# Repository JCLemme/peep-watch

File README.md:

# peep watch

I'm attempting to build some real nice rebbleos hardware. 

---

## the watches

Right now there's just the "big board" prototype. After that there'll be a smaller prototype that can actually be worn on the body and then, hopefully, an actually small watch. (assuming all the prototypes work as designed lol).

## contributing

Hit me up on the discord, documentation is still pretty light.

Datasheets go in ./common/datasheets, kicad libraries in ./common/kicad-libs. I've been using the nightly kicad 5.99 builds.

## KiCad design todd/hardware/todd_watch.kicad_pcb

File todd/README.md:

# "todd" prototype watch

Ok so this is the "big board" prototype. Everything broken out, huge pcb, erring on the side of excess, etc. Hopefully this design can just be taken and crammed onto a tiny lil board when we're ready to make some wearable prototypes.

[See the schematic here](./sch_export/todd_watch.pdf)

---

## theory of design

I'm trying to not stray too far from the designs of the original run of pebbles. I'm all in for messing with the "formula" in the future but right now we need more of the same, yeah? With that in mind the feature set hits the same notes:

* 32bit ARM cpu @ 128mhz with ~512k RAM
* 64mb flash storage
* JDI memory-in-pixel transflective LCD
* Four buttons
* IMU with magnetometer, gyroscope, etc.
* Microphone

It's a good starting place anyway. I'm not too worried about part commonality (practical reasons, the pebbles are getting up there in years) and once I abandoned that mindset things got wild. With that in mind -

## the changes

In no particular order

* The cpu was switched over from an STM32 to a shiny new Nordic part, the nRF5340. Along with the obvious improvements - more memory, more flash, more faster - it's a combo cpu + bluetooth part, so we don't need a separate bluetooth chip. It also has a dedicated networking core which might be useful for power reduction going forward.
* The display is a 176x176 model, up from 168x144. It's the closest display I could find to the originals.
* The IMU has a magnetometer built in - one fewer chip.
* The PMIC includes all the battery hardware, plus a haptic controller. Also about that -
* Swapped the ERM vibration motor for a linear resonant actuator. Welcome to the future bay bee
* NFC is also built into the cpu, so tap to pay might be a potential feature. Maybe. Hopefully.

## back to theory

I'd like this design to stay relevant and sourceable for a while so I'm choosing parts by what I can trust will be available long term. As of right now all the parts chosen are in stock at digikey, normally stocked by digikey, and have at least five years of availability on the roadmap. (Save for the display - it's in stock at arrow right now but it's a weird part with no good replacement so).

The board is gonna be big to support all the extra jumpers and breakouts and whatnot but it's gonna use the same packages (ideally) as the small version. These are gonna be nasty little BGAs and QFNs which means that most people won't be able to build one but them's the breaks. When everything is working I'm down to do a little manufacturing run with my oven, get some hardware to people.

---

## so does it work

Not yet

## when will it work

June, probably

## what's done

Schematic is looking good. Working on BOM and footprints now

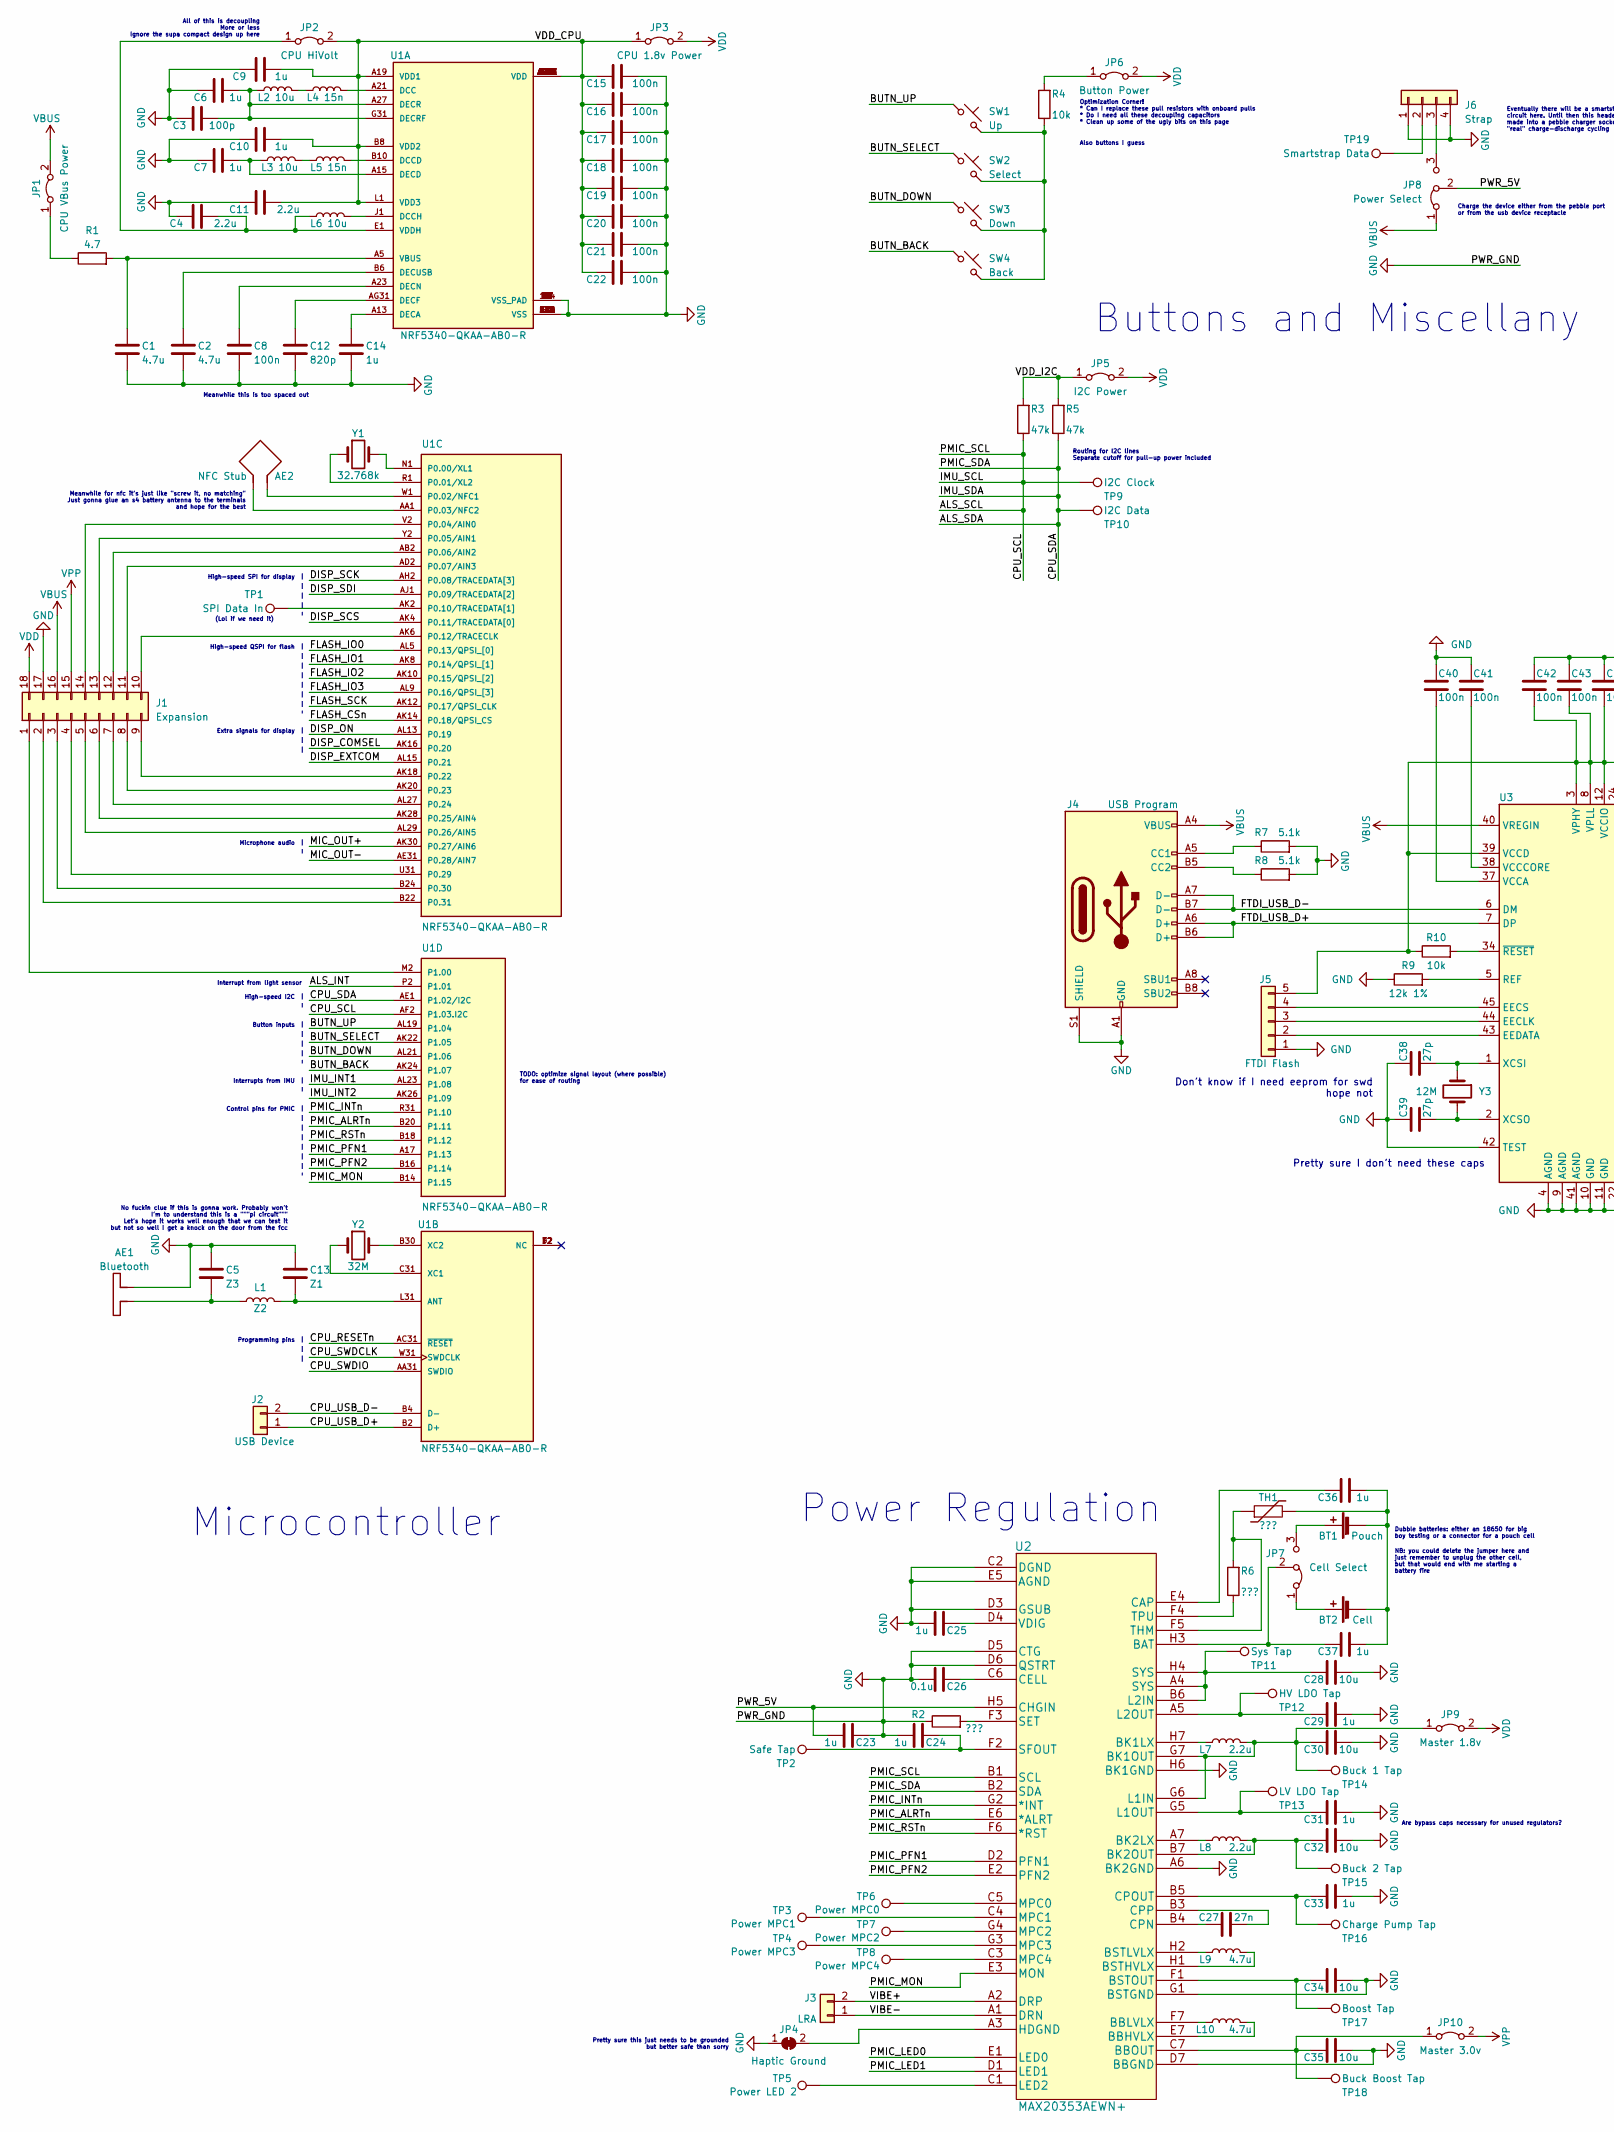
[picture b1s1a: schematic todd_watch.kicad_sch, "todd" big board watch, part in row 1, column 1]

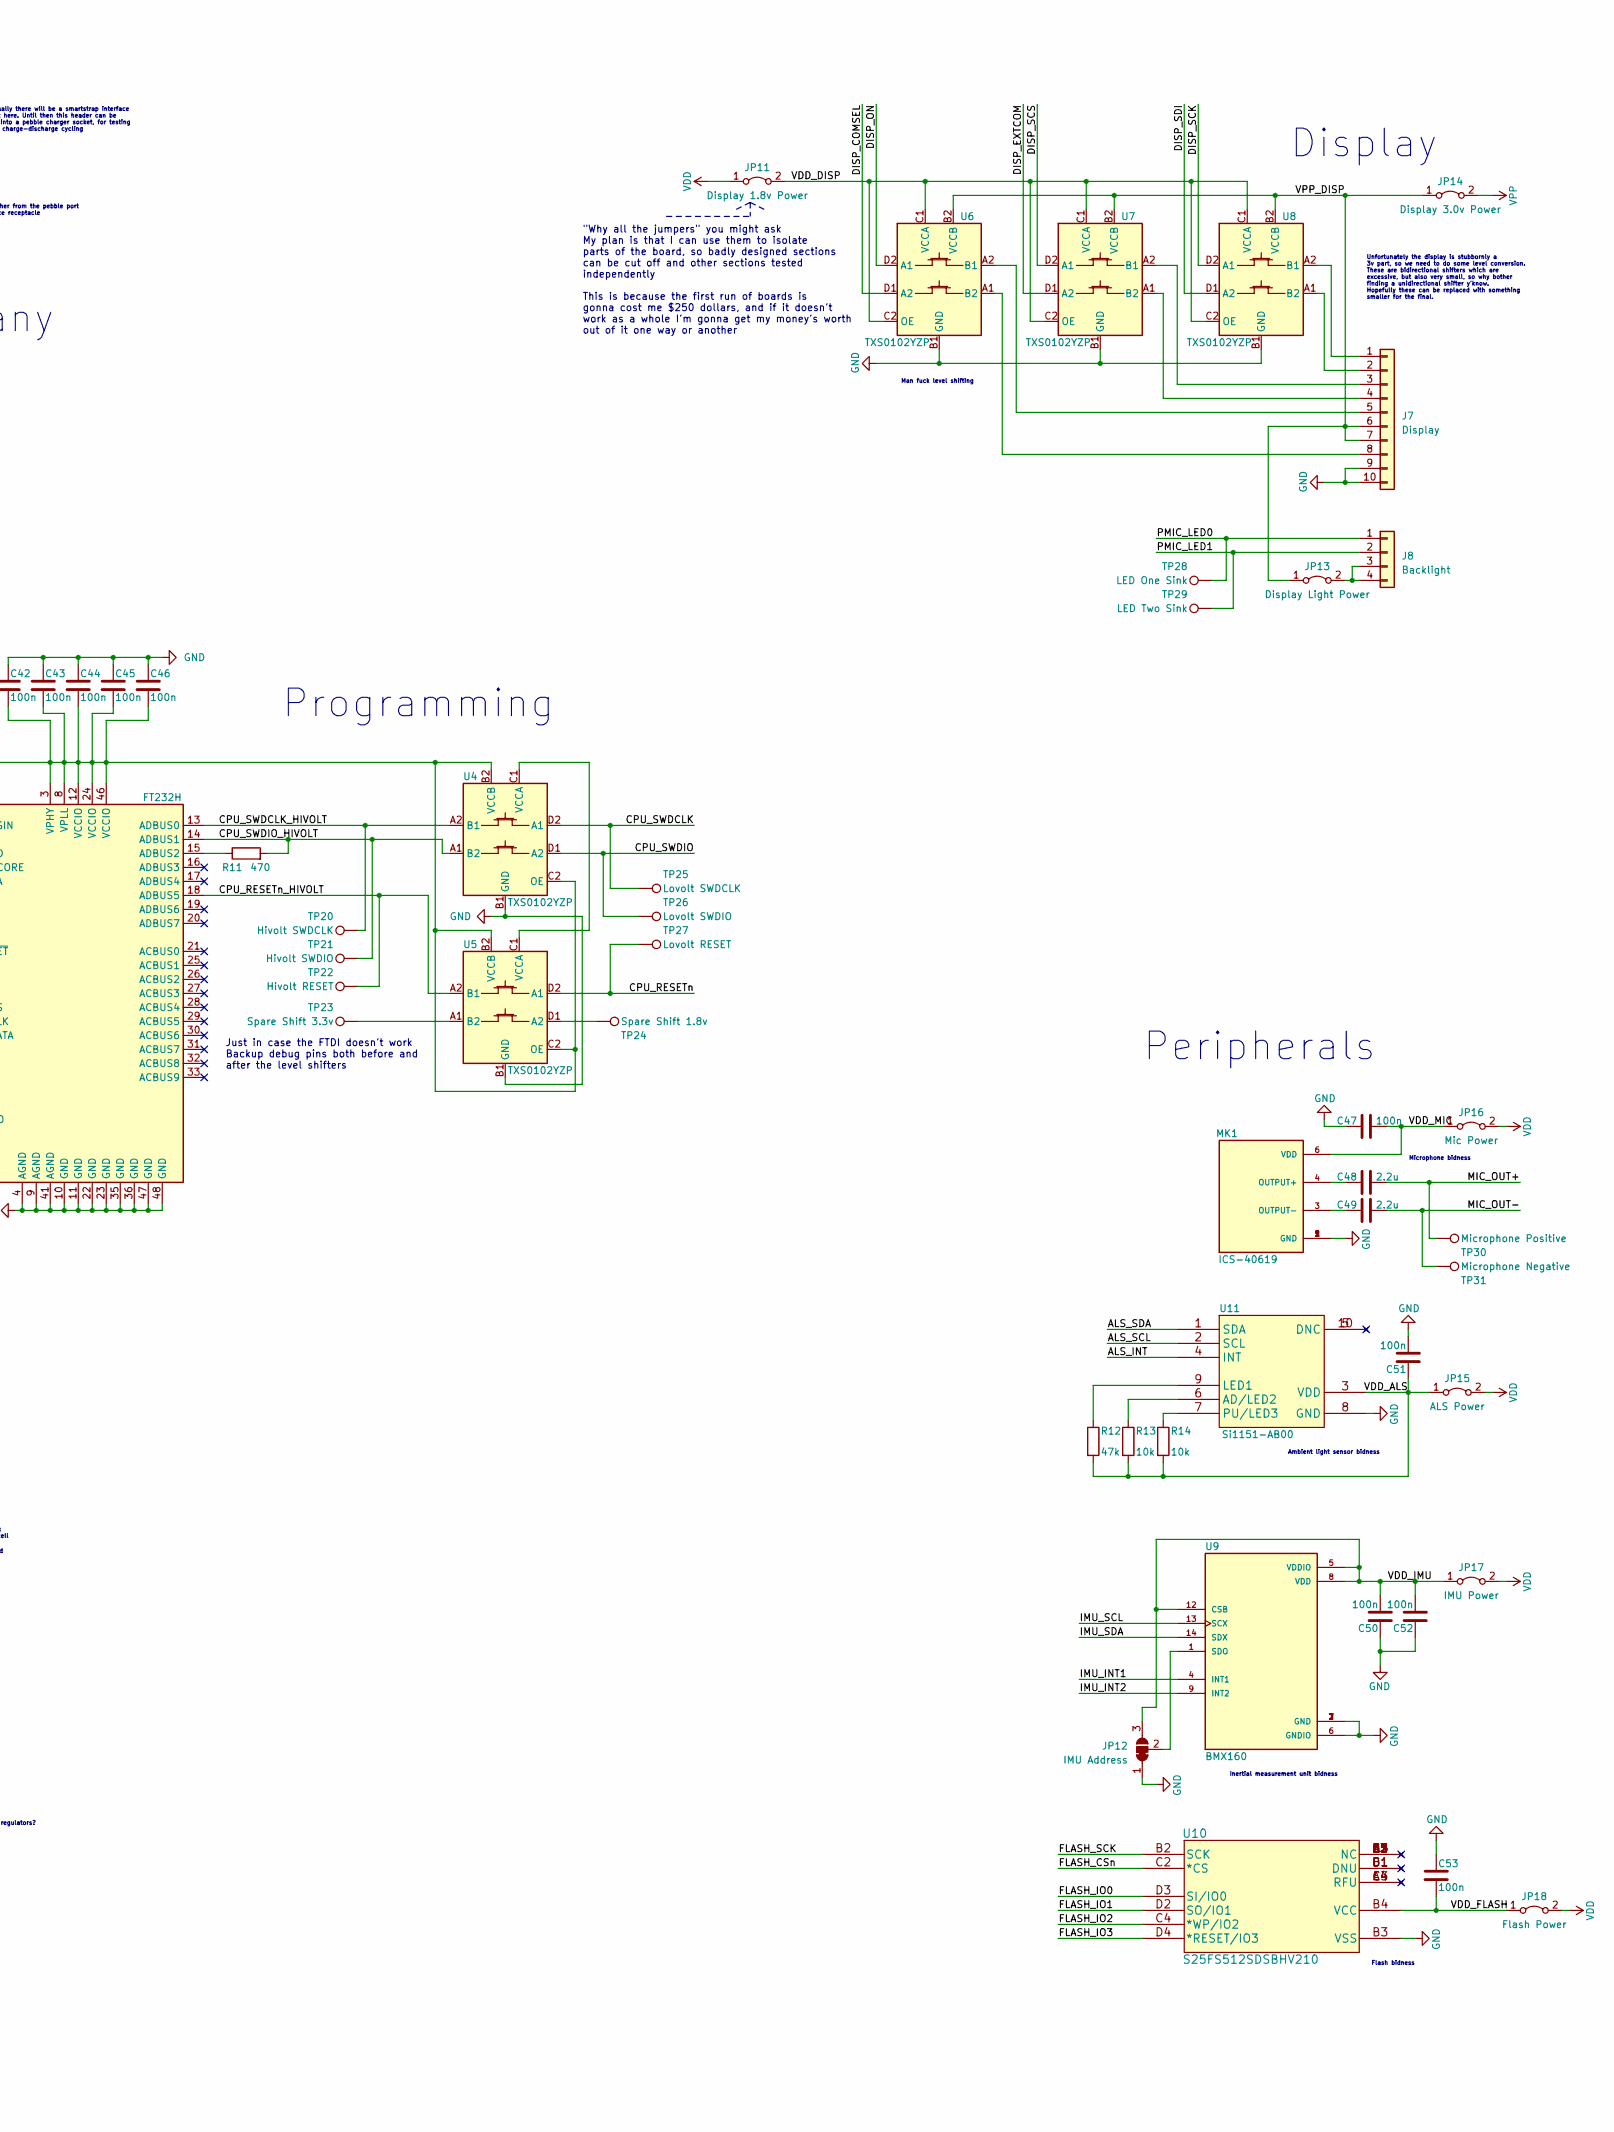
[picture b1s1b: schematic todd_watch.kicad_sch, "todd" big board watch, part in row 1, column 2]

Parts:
AE1: Bluetooth; Texas_SWRA117D_2.4GHz_Left
AE2: NFC Stub; R_1206_3216Metric_Pad1.30x1.75mm_HandSolder
BT1: Pouch; PinSocket_1x02_P2.54mm_Vertical
BT2: Cell; BatteryHolder_Keystone_1042_1x18650
C1, C2: 4.7u; C_0603_1608Metric
C3: 100p; C_0603_1608Metric
C4, C11, C48, C49: 2.2u; C_0603_1608Metric
C5: Z3; C_0603_1608Metric
C6, C7, C9, C10, C14, C23, C24, C25, C29, C31, C33, C36, C37: 1u; C_0603_1608Metric
C8, C15, C16, C17, C18, C19, C20, C21, C22, C40, C41, C42, C43, C44, C45, C46, C47, C50, C51, C52, C53: 100n; C_0603_1608Metric
C12: 820p; C_0603_1608Metric
C13: Z1; C_0603_1608Metric
C26: 0.1u; C_0603_1608Metric
C27: 27n; C_0603_1608Metric
C28, C30, C32, C34, C35: 10u; C_0603_1608Metric
C38, C39: 27p; C_0603_1608Metric
J1: Expansion; PinSocket_2x09_P1.27mm_Vertical
J2: USB Device
J3: LRA; PinHeader_1x02_P2.54mm_Vertical
J4: USB Program; USB_C_Receptacle_XKB_U262-16XN-4BVC11
J5: FTDI Flash; PinHeader_1x05_P1.27mm_Vertical
J6: Strap; PinHeader_1x04_P2.54mm_Vertical
J7: Display; Hirose_FH12-10S-0.5SH_1x10-1MP_P0.50mm_Horizontal
J8: Backlight
JP1: CPU VBus Power; PinHeader_2x01_P1.27mm_Horizontal
JP2: CPU HiVolt; PinHeader_2x01_P1.27mm_Horizontal
JP3: CPU 1.8v Power; PinHeader_2x01_P1.27mm_Horizontal
JP4: Haptic Ground; SolderJumper-2_P1.3mm_Open_TrianglePad1.0x1.5mm
JP5: I2C Power; PinHeader_2x01_P1.27mm_Horizontal
JP6: Button Power; PinHeader_2x01_P1.27mm_Horizontal
JP7: Cell Select; PinHeader_1x03_P1.27mm_Horizontal
JP8: Power Select; PinHeader_1x03_P1.27mm_Horizontal
JP9: Master 1.8v; PinHeader_2x01_P1.27mm_Horizontal
JP10: Master 3.0v; PinHeader_1x02_P1.27mm_Horizontal
JP11: Display 1.8v Power; PinHeader_1x02_P1.27mm_Horizontal
JP12: IMU Address; SolderJumper-3_P2.0mm_Open_TrianglePad1.0x1.5mm_NumberLabels
JP13: Display Light Power; PinHeader_1x02_P1.27mm_Horizontal
JP14: Display 3.0v Power; PinHeader_1x02_P1.27mm_Horizontal
JP15: ALS Power; PinHeader_1x02_P1.27mm_Horizontal
JP16: Mic Power; PinHeader_1x02_P1.27mm_Horizontal
JP17: IMU Power; PinHeader_1x02_P1.27mm_Horizontal
JP18: Flash Power; PinHeader_1x02_P1.27mm_Horizontal
L1: Z2; L_0603_1608Metric
L2, L3, L6: 10u; L_0603_1608Metric
L4, L5: 15n; L_0603_1608Metric
L7, L8: 2.2u; L_0603_1608Metric
L9, L10: 4.7u; L_0603_1608Metric
MK1: ICS-40619; MIC_ICS-40619; PARTREV 1.0
R1: 4.7; R_0603_1608Metric
R2, R6: ???; R_0603_1608Metric
R3, R5, R12: 47k; R_0603_1608Metric
R4, R10, R13, R14: 10k; R_0603_1608Metric
R7, R8: 5.1k; R_0603_1608Metric
R9: 12k 1%; R_0603_1608Metric
R11: 470; R_0603_1608Metric
SW1: Up; SW_PUSH_6mm
SW2: Select; SW_PUSH_6mm
SW3: Down; SW_PUSH_6mm
SW4: Back; SW_PUSH_6mm
TH1: ???; C_0603_1608Metric
TP1: SPI Data In; TestPoint_Pad_D1.0mm
TP2: Safe Tap; TestPoint_Pad_D1.0mm
TP3: Power MPC1; TestPoint_Pad_D1.0mm
TP4: Power MPC3; TestPoint_Pad_D1.0mm
TP5: Power LED 2; TestPoint_Pad_D1.0mm
TP6: Power MPC0; TestPoint_Pad_D1.0mm
TP7: Power MPC2; TestPoint_Pad_D1.0mm
TP8: Power MPC4; TestPoint_Pad_D1.0mm
TP9: I2C Clock; TestPoint_Pad_D1.0mm
TP10: I2C Data; TestPoint_Pad_D1.0mm
TP11: Sys Tap; TestPoint_Pad_D1.0mm
TP12: HV LDO Tap; TestPoint_Pad_D1.0mm
TP13: LV LDO Tap; TestPoint_Pad_D1.0mm
TP14: Buck 1 Tap; TestPoint_Pad_D1.0mm
TP15: Buck 2 Tap; TestPoint_Pad_D1.0mm
TP16: Charge Pump Tap; TestPoint_Pad_D1.0mm
TP17: Boost Tap; TestPoint_Pad_D1.0mm
TP18: Buck Boost Tap; TestPoint_Pad_D1.0mm
TP19: Smartstrap Data; TestPoint_Pad_D1.0mm
TP20: Hivolt SWDCLK; TestPoint_Pad_D1.0mm
TP21: Hivolt SWDIO; TestPoint_Pad_D1.0mm
TP22: Hivolt RESET; TestPoint_Pad_D1.0mm
TP23: Spare Shift 3.3v; TestPoint_Pad_D1.0mm
TP24: Spare Shift 1.8v; TestPoint_Pad_D1.0mm
TP25: Lovolt SWDCLK; TestPoint_Pad_D1.0mm
TP26: Lovolt SWDIO; TestPoint_Pad_D1.0mm
TP27: Lovolt RESET; TestPoint_Pad_D1.0mm
TP28: LED One Sink; TestPoint_Pad_D1.0mm
TP29: LED Two Sink; TestPoint_Pad_D1.0mm
TP30: Microphone Positive; TestPoint_Pad_D1.0mm
TP31: Microphone Negative; TestPoint_Pad_D1.0mm
U1: NRF5340-QKAA-AB0-R; XCVR_NRF5340-QKAA-AB0-R; PARTREV 1.0
U2: MAX20353AEWN+; MAX20353AEWN&plus_
U3: FT232H; LQFP-48_7x7mm_P0.5mm
U4, U5, U6, U7, U8: TXS0102YZP; Texas_DSBGA-8_0.9x1.9mm_Layout2x4_P0.5mm
U9: BMX160; PQFN50P250X300X100-14N; PARTREV 1.2
U10: S25FS512SDSBHV210; S25FL512SAGBHIC10
U11: Si1151-AB00; 10-WFQFN
Y1: 32.768k; Crystal_SMD_2012-2Pin_2.0x1.2mm
Y2: 32M; Crystal_SMD_2012-2Pin_2.0x1.2mm
Y3: 12M; Crystal_SMD_2012-2Pin_2.0x1.2mm

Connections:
/ALS_INT: U1.P2 (P1.01), U11.4 (INT)
/ALS_SCL: R3.1, TP9.1, U1.AF2 (P1.03.I2C), U2.B1 (SCL), U9.13 (SCX), U11.2 (SCL)
/ALS_SDA: R5.1, TP10.1, U1.AE1 (P1.02/I2C), U2.B2 (SDA), U9.14 (SDX), U11.1 (SDA)
/BUTN_BACK: SW4.1, U1.AK24 (P1.07)
/BUTN_DOWN: SW3.1, U1.AL21 (P1.06)
/BUTN_SELECT: SW2.1, U1.AK22 (P1.05)
/BUTN_UP: SW1.1, U1.AL19 (P1.04)
/CPU_RESETn: TP27.1, U1.AC31 (~RESET), U5.D2 (A1)
/CPU_RESETn_HIVOLT: TP22.1, U3.18 (ADBUS5), U5.A2 (B1)
/CPU_SWDCLK: TP25.1, U1.W31 (SWDCLK), U4.D2 (A1)
/CPU_SWDCLK_HIVOLT: TP20.1, U3.13 (ADBUS0), U4.A2 (B1)
/CPU_SWDIO: TP26.1, U1.AA31 (SWDIO), U4.D1 (A2)
/CPU_SWDIO_HIVOLT: R11.2, TP21.1, U3.14 (ADBUS1), U4.A1 (B2)
/CPU_USB_D+: J2.1, U1.B2 (D+)
/CPU_USB_D-: J2.2, U1.B4 (D-)
/DISP_COMSEL: U1.AK16 (P0.20), U6.D1 (A2)
/DISP_EXTCOM: U1.AL15 (P0.21), U7.D1 (A2)
/DISP_ON: U1.AL13 (P0.19), U6.D2 (A1)
/DISP_SCK: U1.AH2 (P0.08/TRACEDATA[3]), U8.D2 (A1)
/DISP_SCS: U1.AK4 (P0.11/TRACEDATA[0]), U7.D2 (A1)
/DISP_SDI: U1.AJ1 (P0.09/TRACEDATA[2]), U8.D1 (A2)
/FLASH_CSn: U1.AK14 (P0.18/QPSI_CS), U10.C2 (*CS)
/FLASH_IO0: U1.AL5 (P0.13/QPSI_[0]), U10.D3 (SI/IO0)
/FLASH_IO1: U1.AK8 (P0.14/QPSI_[1]), U10.D2 (SO/IO1)
/FLASH_IO2: U1.AK10 (P0.15/QPSI_[2]), U10.C4 (*WP/IO2)
/FLASH_IO3: U1.AL9 (P0.16/QPSI_[3]), U10.D4 (*RESET/IO3)
/FLASH_SCK: U1.AK12 (P0.17/QPSI_CLK), U10.B2 (SCK)
/FTDI_USB_D+: J4.A6 (D+), J4.B6 (D+), U3.7 (DP)
/FTDI_USB_D-: J4.A7 (D-), J4.B7 (D-), U3.6 (DM)
/IMU_INT1: U1.AL23 (P1.08), U9.4 (INT1)
/IMU_INT2: U1.AK26 (P1.09), U9.9 (INT2)
/MIC_OUT+: C48.1, TP30.1, U1.AK30 (P0.27/AIN6)
/MIC_OUT-: C49.1, TP31.1, U1.AE31 (P0.28/AIN7)
/PMIC_ALRTn: U1.B20 (P1.11), U2.E6 (*ALRT)
/PMIC_INTn: U1.R31 (P1.10), U2.G2 (*INT)
/PMIC_LED0: J8.1, TP28.1, U2.E1 (LED0)
/PMIC_LED1: J8.2, TP29.1, U2.D1 (LED1)
/PMIC_MON: U1.B14 (P1.15), U2.E3 (MON)
/PMIC_PFN1: U1.A17 (P1.13), U2.D2 (PFN1)
/PMIC_PFN2: U1.B16 (P1.14), U2.E2 (PFN2)
/PMIC_RSTn: U1.B18 (P1.12), U2.F6 (*RST)
/PWR_5V: C23.2, JP8.2 (C), U2.H5 (CHGIN)
/VDD_ALS: C51.1, JP15.1 (A), R12.2, R13.2, R14.2, U11.3 (VDD)
/VDD_CPU: C9.2, C10.2, C11.2, C15.1, C16.1, C17.1, C18.1, C19.1, C20.1, C21.1, C22.1, JP2.2 (B), JP3.1 (A), U1.A19 (VDD1), U1.AC1 (VDD), U1.AG1 (VDD), U1.AJ31 (VDD), U1.AL3 (VDD), U1.AL7 (VDD), U1.AL11 (VDD), U1.AL17 (VDD), U1.AL25 (VDD), U1.B8 (VDD2), U1.B28 (VDD), U1.C1 (VDD), U1.E31 (VDD), U1.L1 (VDD3), U1.N31 (VDD), U1.U1 (VDD)
/VDD_DISP: JP11.2 (B), U6.C1 (VCCA), U6.C2 (OE), U7.C1 (VCCA), U7.C2 (OE), U8.C1 (VCCA), U8.C2 (OE)
/VDD_FLASH: C53.2, JP18.1 (A), U10.B4 (VCC)
/VDD_I2C: JP5.1 (A), R3.2, R5.2
/VDD_IMU: C50.2, C52.2, JP12.3 (B), JP17.1 (A), U9.5 (VDDIO), U9.8 (VDD), U9.12 (CSB)
/VDD_MIC: C47.1, JP16.1 (A), MK1.6 (VDD)
/VIBE+: J3.2, U2.A2 (DRP)
/VIBE-: J3.1, U2.A1 (DRN)
/VPP_DISP: J7.6, J7.7, JP13.1 (A), JP14.1 (A), U6.B2 (VCCB), U7.B2 (VCCB), U8.B2 (VCCB)
GND: AE1.2, C1.2, C2.2, C3.1, C4.1, C5.2, C6.1, C7.1, C8.2, C9.1, C10.1, C11.1, C12.2, C13.2, C14.2, C15.2, C16.2, C17.2, C18.2, C19.2, C20.2, C21.2, C22.2, C23.1, C24.2, C25.2, C26.2, C28.2, C29.2, C30.2, C31.2, C32.2, C33.2, C34.2, C35.2, C38.1, C39.1, C40.1, C41.1, C42.1, C43.1, C44.1, C45.1, C46.1, C47.2, C50.1, C51.2, C52.1, C53.1, J1.17, J4.A1 (GND), J4.A12 (GND), J4.B1 (GND), J4.B12 (GND), J4.S1 (SHIELD), J5.1, J6.1, J6.4, J7.9, J7.10, JP4.1 (A), JP12.1 (A), MK1.1 (GND), MK1.2 (GND), MK1.5 (GND), R2.1, R7.2, R8.2, R9.1, U1.35 (VSS_PAD), U1.36 (VSS_PAD), U1.37 (VSS_PAD), U1.38 (VSS_PAD), U1.39 (VSS_PAD), U1.40 (VSS_PAD), U1.41 (VSS_PAD), U1.43 (VSS_PAD), U1.44 (VSS_PAD), U1.45 (VSS_PAD), U1.46 (VSS_PAD), U1.47 (VSS_PAD), U1.48 (VSS_PAD), U1.49 (VSS_PAD), U1.50 (VSS_PAD), U1.51 (VSS_PAD), U1.104 (VSS_PAD), U1.A25 (VSS), U1.B12 (VSS), U1.B26 (VSS), U1.G1 (VSS), U1.H2 (VSS), U1.J31 (VSS), U2.A6 (BK2GND), U2.C2 (DGND), U2.D3 (GSUB), U2.D5 (CTG), U2.D6 (QSTRT), U2.D7 (BBGND), U2.E5 (AGND), U2.G1 (BSTGND), U2.H6 (BK1GND), U3.4 (AGND), U3.9 (AGND), U3.10 (GND), U3.11 (GND), U3.22 (GND), U3.23 (GND), U3.35 (GND), U3.36 (GND), U3.41 (AGND), U3.42 (TEST), U3.47 (GND), U3.48 (GND), U4.B1 (GND), U5.B1 (GND), U6.B1 (GND), U7.B1 (GND), U8.B1 (GND), U9.2 (GND), U9.3 (GND), U9.6 (GNDIO), U9.7 (GND), U10.B3 (VSS), U11.8 (GND)
unnamed: AE1.1, C5.1, L1.1
unnamed: AE2.1, U1.AA1 (P0.03/NFC2)
unnamed: AE2.2, U1.W1 (P0.02/NFC1)
unnamed: BT1.1 (+), JP7.3 (B)
unnamed: BT1.2 (-), BT2.2 (-), C36.2, C37.2, TH1.2
unnamed: BT2.1 (+), JP7.1 (A)
unnamed: C1.1, R1.2, U1.A5 (VBUS)
unnamed: C2.1, U1.B6 (DECUSB)
unnamed: C3.2, C6.2, L2.1, U1.A27 (DECR), U1.G31 (DECRF)
unnamed: C4.2, JP2.1 (A), L6.1, U1.E1 (VDDH)
unnamed: C7.2, L3.1, U1.A15 (DECD)
unnamed: C8.1, U1.A23 (DECN)
unnamed: C12.1, U1.AG31 (DECF)
unnamed: C13.1, L1.2, U1.L31 (ANT)
unnamed: C14.1, U1.A13 (DECA)
unnamed: C24.1, TP2.1, U2.F2 (SFOUT)
unnamed: C25.1, U2.D4 (VDIG)
unnamed: C26.1, U2.C6 (CELL)
unnamed: C27.1, U2.B4 (CPN)
unnamed: C27.2, U2.B3 (CPP)
unnamed: C28.1, TP11.1, U2.A4 (SYS), U2.B6 (L2IN), U2.H4 (SYS)
unnamed: C29.1, TP12.1, U2.A5 (L2OUT)
unnamed: C30.1, JP9.1 (A), L7.2, TP14.1, U2.G6 (L1IN), U2.G7 (BK1OUT)
unnamed: C31.1, TP13.1, U2.G5 (L1OUT)
unnamed: C32.1, L8.2, TP15.1, U2.B7 (BK2OUT)
unnamed: C33.1, TP16.1, U2.B5 (CPOUT)
unnamed: C34.1, TP17.1, U2.F1 (BSTOUT)
unnamed: C35.1, JP10.1 (A), TP18.1, U2.C7 (BBOUT)
unnamed: C36.1, U2.E4 (CAP)
unnamed: C37.1, JP7.2 (C), U2.H3 (BAT)
unnamed: C38.2, U3.1 (XCSI), Y3.1
unnamed: C39.2, U3.2 (XCSO), Y3.2
unnamed: C40.2, U3.37 (VCCA)
unnamed: C41.2, U3.38 (VCCCORE)
unnamed: C42.2, C43.2, C44.2, C45.2, C46.2, J5.5, R10.1, U3.3 (VPHY), U3.8 (VPLL), U3.12 (VCCIO), U3.24 (VCCIO), U3.39 (VCCD), U3.46 (VCCIO), U4.B2 (VCCB), U4.C2 (OE), U5.B2 (VCCB), U5.C2 (OE)
unnamed: C48.2, MK1.4 (OUTPUT+)
unnamed: C49.2, MK1.3 (OUTPUT-)
unnamed: J1.1, U1.M2 (P1.00)
unnamed: J1.2, U1.B22 (P0.31)
unnamed: J1.3, U1.B24 (P0.30)
unnamed: J1.4, U1.U31 (P0.29)
unnamed: J1.5, U1.AL29 (P0.26/AIN5)
unnamed: J1.6, U1.AK28 (P0.25/AIN4)
unnamed: J1.7, U1.AL27 (P0.24)
unnamed: J1.8, U1.AK20 (P0.23)
unnamed: J1.9, U1.AK18 (P0.22)
unnamed: J1.10, U1.AK6 (P0.12/TRACECLK)
unnamed: J1.11, U1.AD2 (P0.07/AIN3)
unnamed: J1.12, U1.AB2 (P0.06/AIN2)
unnamed: J1.13, U1.Y2 (P0.05/AIN1)
unnamed: J1.14, U1.V2 (P0.04/AIN0)
unnamed: J4.A5 (CC1), R7.1
unnamed: J4.B5 (CC2), R8.1
unnamed: J5.2, U3.43 (EEDATA)
unnamed: J5.3, U3.44 (EECLK)
unnamed: J5.4, U3.45 (EECS)
unnamed: J6.2, TP19.1
unnamed: J6.3, JP8.3 (B)
unnamed: J7.1, U8.A2 (B1)
unnamed: J7.2, U8.A1 (B2)
unnamed: J7.3, U7.A2 (B1)
unnamed: J7.4, U7.A1 (B2)
unnamed: J7.5, U6.A2 (B1)
unnamed: J7.8, U6.A1 (B2)
unnamed: J8.3, J8.4, JP13.2 (B)
unnamed: JP1.1 (A), R1.1
unnamed: JP4.2 (B), U2.A3 (HDGND)
unnamed: JP6.1 (A), R4.2
unnamed: JP12.2 (C), U9.1 (SDO)
unnamed: L2.2, L4.1
unnamed: L3.2, L5.1
unnamed: L4.2, U1.A21 (DCC)
unnamed: L5.2, U1.B10 (DCCD)
unnamed: L6.2, U1.J1 (DCCH)
unnamed: L7.1, U2.H7 (BK1LX)
unnamed: L8.1, U2.A7 (BK2LX)
unnamed: L9.1, U2.H2 (BSTLVLX)
unnamed: L9.2, U2.H1 (BSTHVLX)
unnamed: L10.1, U2.F7 (BBLVLX)
unnamed: L10.2, U2.E7 (BBHVLX)
unnamed: R2.2, U2.F3 (SET)
unnamed: R4.1, SW1.2, SW2.2, SW3.2, SW4.2
unnamed: R6.1, U2.F4 (TPU)
unnamed: R6.2, TH1.1, U2.F5 (THM)
unnamed: R9.2, U3.5 (REF)
unnamed: R10.2, U3.34 (~RESET)
unnamed: R11.1, U3.15 (ADBUS2)
unnamed: R12.1, U11.9 (LED1)
unnamed: R13.1, U11.6 (AD/LED2)
unnamed: R14.1, U11.7 (PU/LED3)
unnamed: TP1.1, U1.AK2 (P0.10/TRACEDATA[1])
unnamed: TP3.1, U2.C4 (MPC1)
unnamed: TP4.1, U2.G3 (MPC3)
unnamed: TP5.1, U2.C1 (LED2)
unnamed: TP6.1, U2.C5 (MPC0)
unnamed: TP7.1, U2.G4 (MPC2)
unnamed: TP8.1, U2.C3 (MPC4)
unnamed: TP23.1, U5.A1 (B2)
unnamed: TP24.1, U5.D1 (A2)
unnamed: U1.B30 (XC2), Y2.2
unnamed: U1.C31 (XC1), Y2.1
unnamed: U1.N1 (P0.00/XL1), Y1.2
unnamed: U1.R1 (P0.01/XL2), Y1.1
unnamed: U4.C1 (VCCA), U5.C1 (VCCA)
VBUS: J1.16, J4.A4 (VBUS), J4.A9 (VBUS), J4.B4 (VBUS), J4.B9 (VBUS), JP1.2 (B), JP8.1 (A), U3.40 (VREGIN)
VDD: J1.18, JP3.2 (B), JP5.2 (B), JP6.2 (B), JP9.2 (B), JP11.1 (A), JP15.2 (B), JP16.2 (B), JP17.2 (B), JP18.2 (B)
VPP: J1.15, JP10.2 (B), JP14.2 (B)

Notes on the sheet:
Microcontroller
Meanwhile for nfc it's just like "screw it, no matching" Just gonna glue an s4 battery antenna to the terminals and hope for the best
All of this is decoupling More or less Ignore the supa compact design up here
(Lol if we need it)
No fuckin clue if this is gonna work. Probably won't I'm to understand this is a """pi circuit""" Let's hope it works well enough that we can test it but not so well I get a knock on the door from the fcc
High-speed SPI for display
High-speed QSPI for flash
Extra signals for display
Microphone audio
High-speed I2C
Button inputs
Interrupts from IMU
Control pins for PMIC
Programming pins
Interrupt from light sensor
Meanwhile this is too spaced out
TODO: optimize signal layout (where possible) for ease of routing
Pretty sure this just needs to be grounded but better safe than sorry
Power Regulation
Routing for I2C lines Separate cutoff for pull-up power included
Optimization Corner! * Can I replace these pull resistors with onboard pulls * Do I need all these decoupling capacitors * Clean up some of the ugly bits on this page
Also buttons I guess
Buttons and Miscellany
Don't know if I need eeprom for swd hope not
Dubble batteries: either an 18650 for big boy testing or a connector for a pouch cell
NB: you could delete the jumper here and just remember to unplug the other cell, but that would end with me starting a battery fire
Are bypass caps necessary for unused regulators?
Charge the device either from the pebble port or from the usb device receptacle
Pretty sure I don't need these caps
Eventually there will be a smartstrap interface circuit here. Until then this header can be made into a pebble charger socket, for testing "real" charge-discharge cycling
Just in case the FTDI doesn't work Backup debug pins both before and after the level shifters
Programming
"Why all the jumpers" you might ask My plan is that I can use them to isolate parts of the board, so badly designed sections can be cut off and other sections tested independently
This is because the first run of boards is gonna cost me $250 dollars, and if it doesn't work as a whole I'm gonna get my money's worth out of it one way or another
Man fuck level shifting
Peripherals
Display
Inertial measurement unit bidness
Unfortunately the display is stubbornly a 3v part, so we need to do some level conversion. These are bidirectional shifters which are excessive, but also very small, so why bother finding a unidirectional shifter y'know. Hopefully these can be replaced with something smaller for the final.
Ambient light sensor bidness

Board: 2 copper layers, 156 parts (0 on the bottom side), 157 nets, no tracks yet.

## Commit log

2021-08-21 Schem 1 done

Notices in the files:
parts and their libraries:
Copyright 2016 Accelerated Designs. All rights reserved.
